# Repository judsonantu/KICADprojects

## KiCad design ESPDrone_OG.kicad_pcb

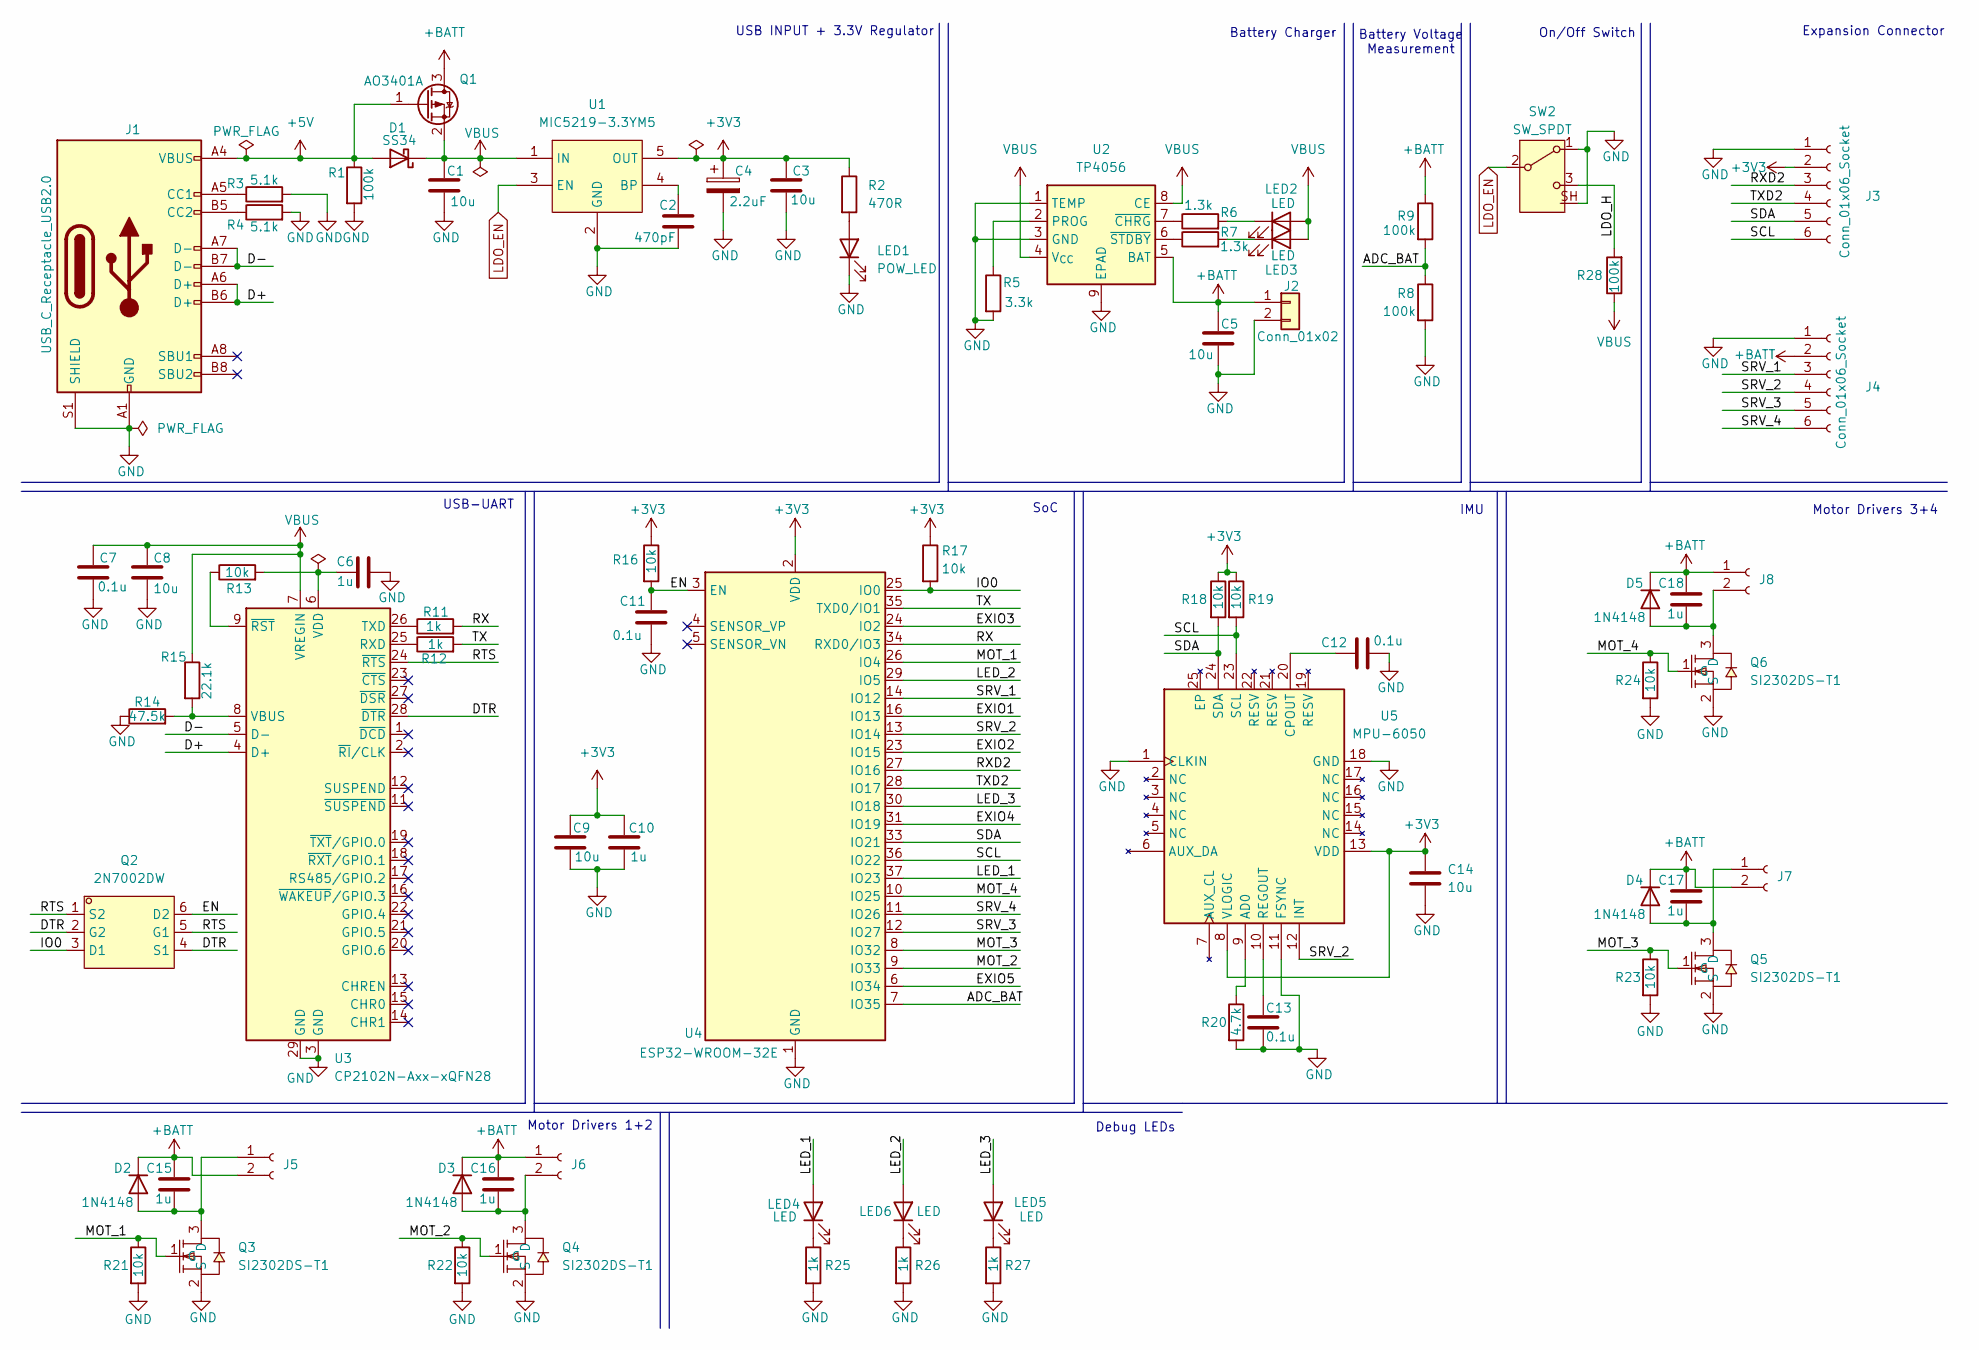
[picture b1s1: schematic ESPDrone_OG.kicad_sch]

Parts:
C1, C3, C5, C8, C9, C14: 10u; C_0603_1608Metric
C2: 470pF; C_0603_1608Metric
C4: 2.2uF; C_0805_2012Metric
C6, C10, C15, C16, C17, C18: 1u; C_0603_1608Metric
C7, C11, C12, C13: 0.1u; C_0603_1608Metric
D1: SS34; D_SMA
D2, D3, D4, D5: 1N4148; D_SOD-323
J1: USB_C_Receptacle_USB2.0; USB_C_Receptacle_G-Switch_GT-USB-7010ASV
J2: Conn_01x02; JST_PH_B2B-PH-SM4-TB_1x02-1MP_P2.00mm_Vertical
J3, J4: Conn_01x06_Socket; PinHeader_1x06_P2.54mm_Vertical
J5, J6, J7, J8: Conn_01x02_Socket; JST_GH_SM02B-GHS-TB_1x02-1MP_P1.25mm_Horizontal
LED1: POW_LED; LED_0603_1608Metric
LED2, LED3, LED4, LED5, LED6: LED; LED_0603_1608Metric
Q1: AO3401A; SOT-23
Q2: 2N7002DW; SOT-363-6_L2.0-W1.3-P0.65-LS2.1-BL; MPN 2N7002DW; LCSC Part C232839
Q3, Q4, Q5, Q6: SI2302DS-T1; SOT-23-3; MPN SI2302DS-T1-GE3-ES; LCSC Part C5224184
R1, R8, R9, R28: 100k; R_0603_1608Metric
R2: 470R; R_0603_1608Metric
R3, R4: 5.1k; R_0603_1608Metric
R5: 3.3k; R_0603_1608Metric
R6, R7: 1.3k; R_0603_1608Metric
R11, R12, R25, R26, R27: 1k; R_0603_1608Metric
R13, R16, R17, R18, R19, R21, R22, R23, R24: 10k; R_0603_1608Metric
R14: 47.5k; R_0603_1608Metric
R15: 22.1k; R_0603_1608Metric
R20: 4.7k; R_0603_1608Metric
SW2: SW_SPDT; SW_SPDT_Shouhan_MSK12C02
U1: MIC5219-3.3YM5; SOT-23-5_L3.0-W1.7-P0.95-LS2.8-TL; MPN MIC5219-3.3YM5-TR; LCSC Part C29613
U2: TP4056; SOIC-8-1EP_3.9x4.9mm_P1.27mm_EP2.41x3.3mm_ThermalVias
U3: CP2102N-Axx-xQFN28; QFN-28-1EP_5x5mm_P0.5mm_EP3.35x3.35mm
U4: ESP32-WROOM-32E; ESP32-WROOM-32D
U5: MPU-6050; InvenSense_QFN-24_4x4mm_P0.5mm

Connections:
+3V3: C3.1, C4.1, C9.1, C10.1, C14.1, J3.2, R2.1, R16.1, R17.1, R18.1, R19.1, U1.5 (OUT), U4.2 (VDD), U5.8 (VLOGIC), U5.13 (VDD); also elsewhere on the board
+5V: D1.2 (A), J1.A4 (VBUS), J1.A9 (VBUS), J1.B4 (VBUS), J1.B9 (VBUS), Q1.1 (G), R1.1; also elsewhere on the board
+BATT: C5.1, C15.1, C16.1, C17.1, C18.1, D2.1 (K), D3.1 (K), D4.1 (K), D5.1 (K), J2.1, J4.2, J5.2, J6.1, J7.2, J8.1, Q1.3 (D), R9.1, U2.5 (BAT)
/ADC_BAT: R8.1, R9.2, U4.7 (IO35); also elsewhere on the board
/D+: J1.A6 (D+), J1.B6 (D+), U3.4 (D+); also elsewhere on the board
/D-: J1.A7 (D-), J1.B7 (D-), U3.5 (D-); also elsewhere on the board
/DTR: Q2.2 (G2), Q2.4 (S1), U3.28 (~DTR)
/EN: C11.1, Q2.6 (D2), R16.2, U4.3 (EN); also elsewhere on the board
/IO0: Q2.3 (D1), R17.2, U4.25 (IO0); also elsewhere on the board
/LDO_H: R28.2, SW2.3 (C)
/LED_1: LED4.2 (A), U4.37 (IO23); also elsewhere on the board
/LED_2: LED6.2 (A), U4.29 (IO5); also elsewhere on the board
/LED_3: LED5.2 (A), U4.30 (IO18); also elsewhere on the board
/MOT_1: Q3.1 (G), R21.1, U4.26 (IO4); also elsewhere on the board
/MOT_2: Q4.1 (G), R22.1, U4.9 (IO33); also elsewhere on the board
/MOT_3: Q5.1 (G), R23.1, U4.8 (IO32); also elsewhere on the board
/MOT_4: Q6.1 (G), R24.1, U4.10 (IO25); also elsewhere on the board
/RTS: Q2.1 (S2), Q2.5 (G1), U3.24 (~RTS)
/RX: R11.2, U4.34 (RXD0/IO3); also elsewhere on the board
/RXD2: J3.3, U4.27 (IO16); also elsewhere on the board
/SCL: J3.6, R19.2, U4.36 (IO22), U5.23 (SCL); also elsewhere on the board
/SDA: J3.5, R18.2, U4.33 (IO21), U5.24 (SDA); also elsewhere on the board
/SRV_1: J4.3, U4.14 (IO12); also elsewhere on the board
/SRV_2: J4.4, U4.13 (IO14), U5.12 (INT); also elsewhere on the board
/SRV_3: J4.5, U4.12 (IO27); also elsewhere on the board
/SRV_4: J4.6, U4.11 (IO26); also elsewhere on the board
/TX: R12.2, U4.35 (TXD0/IO1); also elsewhere on the board
/TXD2: J3.4, U4.28 (IO17); also elsewhere on the board
GND: C1.2, C2.2, C3.2, C4.2, C5.2, C6.2, C7.2, C8.2, C9.2, C10.2, C11.2, C12.2, C13.2, C14.2, J1.A1 (GND), J1.A12 (GND), J1.B1 (GND), J1.B12 (GND), J1.S1 (SHIELD), J2.2, J3.1, J4.1, LED1.1 (K), Q3.2 (S), Q4.2 (S), Q5.2 (S), Q6.2 (S), R1.2, R3.2, R4.2, R5.2, R8.2, R14.1, R20.2, R21.2, R22.2, R23.2, R24.2, R25.2, R26.2, R27.2, SW2.1 (A), SW2.SH (D), U1.2 (GND), U2.1 (TEMP), U2.3 (GND), U2.9 (EPAD), U3.3 (GND), U3.29 (GND), U4.1 (GND), U4.15 (GND), U4.38 (GND), U4.39 (GND), U5.1 (CLKIN), U5.11 (FSYNC), U5.18 (GND); also elsewhere on the board
LDO_EN: SW2.2 (B), U1.3 (EN)
unnamed: C15.2, D2.2 (A), J5.1, Q3.3 (D)
unnamed: C16.2, D3.2 (A), J6.2, Q4.3 (D)
unnamed: C17.2, D4.2 (A), J7.1, Q5.3 (D)
unnamed: C18.2, D5.2 (A), J8.2, Q6.3 (D)
unnamed 39: J1.A5 (CC1), R3.1; also elsewhere on the board
unnamed 40: J1.B5 (CC2), R4.1; also elsewhere on the board
unnamed: LED1.2 (A), R2.2
unnamed: LED2.1 (K), R6.2
unnamed: LED3.1 (K), R7.2
unnamed: LED4.1 (K), R25.1
unnamed: LED5.1 (K), R27.1
unnamed: LED6.1 (K), R26.1
unnamed: C2.1, U1.4 (BP)
unnamed: R5.1, U2.2 (PROG)
unnamed: R6.1, U2.7 (~CHRG)
unnamed: R7.1, U2.6 (~STDBY)
unnamed: R12.1, U3.25 (RXD)
unnamed: R11.1, U3.26 (TXD)
unnamed: R14.2, R15.2, U3.8 (VBUS)
unnamed: C6.1, R13.2, U3.6 (VDD)
unnamed: R13.1, U3.9 (~RST)
unnamed: R20.1, U5.9 (AD0)
unnamed: C12.1, U5.20 (CPOUT)
unnamed: C13.1, U5.10 (REGOUT)
VBUS: C1.1, C7.1, C8.1, D1.1 (K), LED2.2 (A), LED3.2 (A), Q1.2 (S), R15.1, R28.1, U1.1 (IN), U2.4 (V_{CC}), U2.8 (CE), U3.7 (VREGIN)

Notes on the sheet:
USB INPUT + 3.3V Regulator
Expansion Connector
Motor Drivers 3+4
USB-UART
Battery Voltage Measurement
Debug LEDs
Motor Drivers 1+2
Battery Charger
SoC
On/Off Switch
IMU

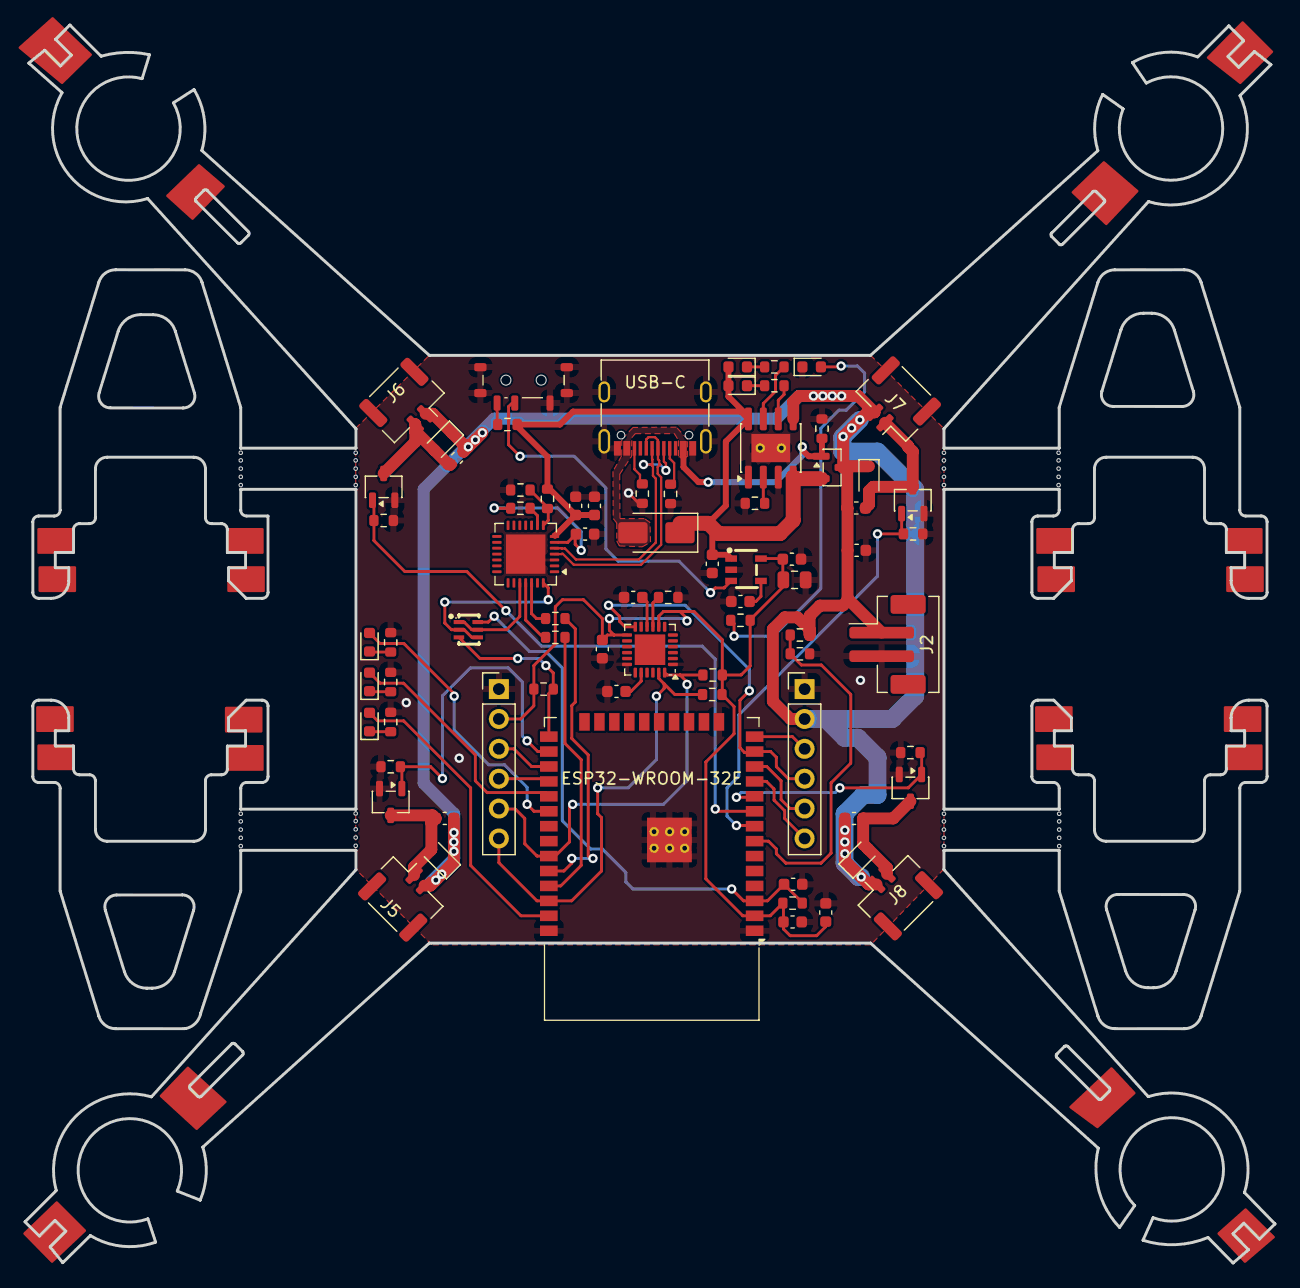
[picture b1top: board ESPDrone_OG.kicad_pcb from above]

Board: 2 copper layers, 106.3 x 105.3 mm, 76 parts (0 on the bottom side), 55 nets.

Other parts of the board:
ESP32-WROOM-32E: ESP32-WROOM-32E; ESP32-WROOM-32D
USB-C: USB_C_Receptacle_USB2.0; USB_C_Receptacle_G-Switch_GT-USB-7010ASV

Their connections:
+3V3: ESP32-WROOM-32E.2 (VDD); also elsewhere on the board
+5V: USB-C.A4 (VBUS), USB-C.A9 (VBUS), USB-C.B4 (VBUS), USB-C.B9 (VBUS); also elsewhere on the board
/ADC_BAT: ESP32-WROOM-32E.7 (IO35); also elsewhere on the board
/D+: USB-C.A6 (D+), USB-C.B6 (D+); also elsewhere on the board
/D-: USB-C.A7 (D-), USB-C.B7 (D-); also elsewhere on the board
/EN: ESP32-WROOM-32E.3 (EN); also elsewhere on the board
/IO0: ESP32-WROOM-32E.25 (IO0); also elsewhere on the board
/LED_1: ESP32-WROOM-32E.37 (IO23); also elsewhere on the board
/LED_2: ESP32-WROOM-32E.29 (IO5); also elsewhere on the board
/LED_3: ESP32-WROOM-32E.30 (IO18); also elsewhere on the board
/MOT_1: ESP32-WROOM-32E.26 (IO4); also elsewhere on the board
/MOT_2: ESP32-WROOM-32E.9 (IO33); also elsewhere on the board
/MOT_3: ESP32-WROOM-32E.8 (IO32); also elsewhere on the board
/MOT_4: ESP32-WROOM-32E.10 (IO25); also elsewhere on the board
/RX: ESP32-WROOM-32E.34 (RXD0/IO3); also elsewhere on the board
/RXD2: ESP32-WROOM-32E.27 (IO16); also elsewhere on the board
/SCL: ESP32-WROOM-32E.36 (IO22); also elsewhere on the board
/SDA: ESP32-WROOM-32E.33 (IO21); also elsewhere on the board
/SRV_1: ESP32-WROOM-32E.14 (IO12); also elsewhere on the board
/SRV_2: ESP32-WROOM-32E.13 (IO14); also elsewhere on the board
/SRV_3: ESP32-WROOM-32E.12 (IO27); also elsewhere on the board
/SRV_4: ESP32-WROOM-32E.11 (IO26); also elsewhere on the board
/TX: ESP32-WROOM-32E.35 (TXD0/IO1); also elsewhere on the board
/TXD2: ESP32-WROOM-32E.28 (IO17); also elsewhere on the board
GND: ESP32-WROOM-32E.1 (GND), ESP32-WROOM-32E.15 (GND), ESP32-WROOM-32E.38 (GND), ESP32-WROOM-32E.39 (GND), USB-C.A1 (GND), USB-C.A12 (GND), USB-C.B1 (GND), USB-C.B12 (GND), USB-C.S1 (SHIELD); also elsewhere on the board
unnamed 39: USB-C.A5 (CC1); also elsewhere on the board
unnamed 40: USB-C.B5 (CC2); also elsewhere on the board

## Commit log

2025-11-19 v1.0
2026-05-18 drone by sachin
2026-05-18 drone files by sachin
